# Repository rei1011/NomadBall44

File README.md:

# NomadBall44

## ライセンス

本リポジトリのオリジナル部分は **GNU General Public License v3**（[LICENSE](LICENSE)）です。

## 第三者ソフトウェア・素材

キーボード設計にあたり、以下のオープンソース／クリエイティブ・コモンズの成果物を利用しています。帰属表示、MIT 全文、GPLv3 との関係、CC BY-SA の条項へのリンクは **[NOTICES](NOTICES)** にまとめています。上流ライセンスのコピーは **[third_party/](third_party/)** にも置いています。

| 名称 | 参照 |
|------|------|
| Salicylic-acid3 / KiCAD_FootPrint（MIT） | https://github.com/Salicylic-acid3/KiCAD_FootPrint |
| koktoh / BrownSugar_KBD_KiCad_Library（MIT） | https://github.com/koktoh/BrownSugar_KBD_KiCad_Library |
| kumamuk-git / roBa（GPL-3.0） | https://github.com/kumamuk-git/roBa |
| Seeed Studio / OPL_Kicad_Library（CC BY-SA 4.0） | https://github.com/Seeed-Studio/OPL_Kicad_Library |

Seeed OPL 由来の KiCad シンボル・フットプリントのファイル一覧、改変内容の説明、および派生ファイルを単体で再配布する際の表示の目安は、**[NOTICES](NOTICES)** のセクション 4 に記載しています。

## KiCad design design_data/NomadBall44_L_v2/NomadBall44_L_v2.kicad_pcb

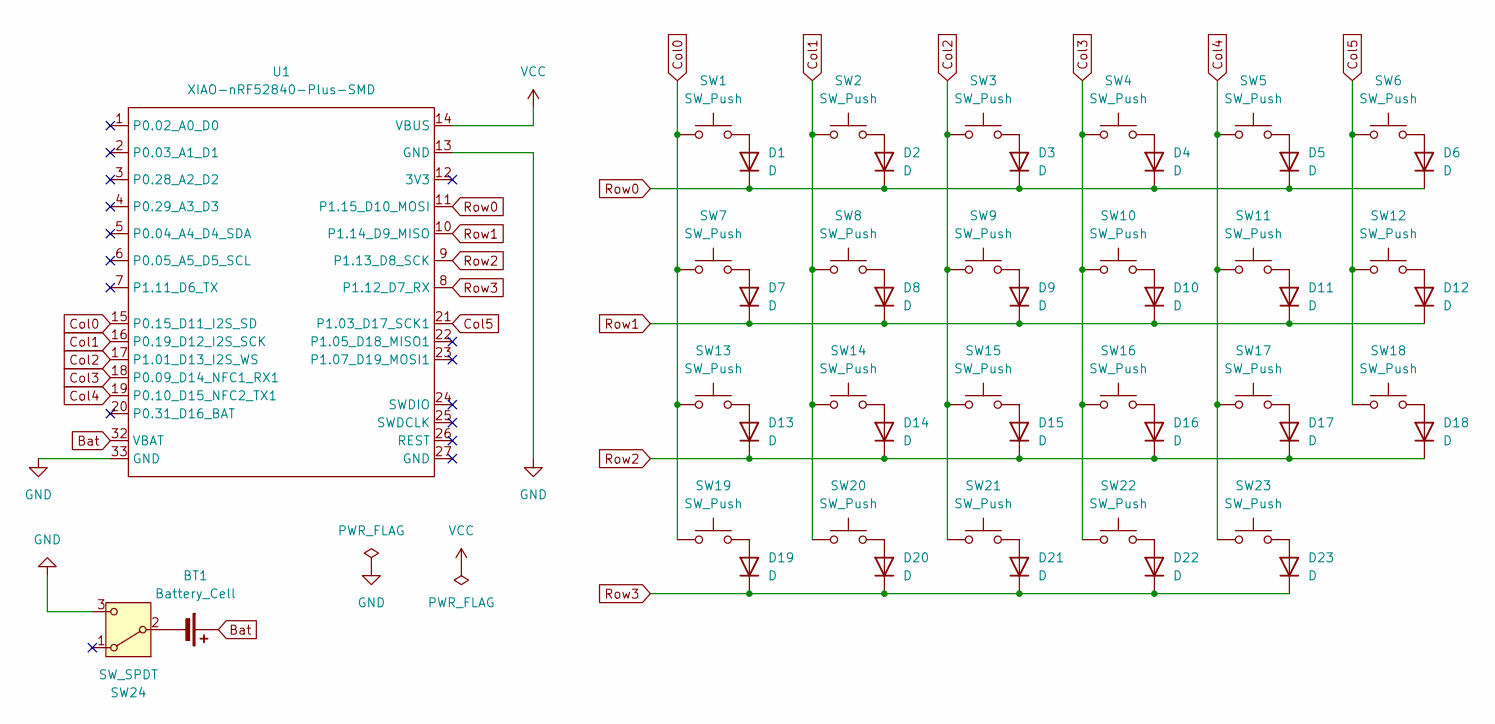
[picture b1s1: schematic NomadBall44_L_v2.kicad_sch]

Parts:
BT1: Battery_Cell; JST_S2B-PH-SM4-TB
D1, D2, D3, D4, D5, D6, D7, D8, D9, D10, D11, D12, D13, D14, D15, D16, D17, D18, D19, D20, D21, D22, D23: D; Diode_SMD
SW1, SW2, SW3, SW4, SW5, SW6, SW7, SW8, SW9, SW10, SW11, SW12, SW13, SW14, SW15, SW16, SW17, SW18, SW19, SW20, SW21, SW22, SW23: SW_Push; Choc_v2_Hotswap_1u
SW24: SW_SPDT; TGSW_MSK-12D19
U1: XIAO-nRF52840-Plus-SMD; XIAO-nRF52840-Plus-ver3

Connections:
Bat: BT1.1 (+), U1.32 (VBAT)
Col0: SW1.1, SW7.1, SW13.1, SW19.1, U1.15 (P0.15_D11_I2S_SD)
Col1: SW2.1, SW8.1, SW14.1, SW20.1, U1.16 (P0.19_D12_I2S_SCK)
Col2: SW3.1, SW9.1, SW15.1, SW21.1, U1.17 (P1.01_D13_I2S_WS)
Col3: SW4.1, SW10.1, SW16.1, SW22.1, U1.18 (P0.09_D14_NFC1_RX1)
Col4: SW5.1, SW11.1, SW17.1, SW23.1, U1.19 (P0.10_D15_NFC2_TX1)
Col5: SW6.1, SW12.1, SW18.1, U1.21 (P1.03_D17_SCK1)
GND: SW24.3 (C), U1.13 (GND), U1.33 (GND)
unnamed: BT1.2 (-), SW24.2 (B)
unnamed: D1.2 (A), SW1.2
unnamed: D2.2 (A), SW2.2
unnamed: D3.2 (A), SW3.2
unnamed: D4.2 (A), SW4.2
unnamed: D5.2 (A), SW5.2
unnamed: D6.2 (A), SW6.2
unnamed: D7.2 (A), SW7.2
unnamed: D8.2 (A), SW8.2
unnamed: D9.2 (A), SW9.2
unnamed: D10.2 (A), SW10.2
unnamed: D11.2 (A), SW11.2
unnamed: D12.2 (A), SW12.2
unnamed: D13.2 (A), SW13.2
unnamed: D14.2 (A), SW14.2
unnamed: D15.2 (A), SW15.2
unnamed: D16.2 (A), SW16.2
unnamed: D17.2 (A), SW17.2
unnamed: D18.2 (A), SW18.2
unnamed: D19.2 (A), SW19.2
unnamed: D20.2 (A), SW20.2
unnamed: D21.2 (A), SW21.2
unnamed: D22.2 (A), SW22.2
unnamed: D23.2 (A), SW23.2
Row0: D1.1 (K), D2.1 (K), D3.1 (K), D4.1 (K), D5.1 (K), D6.1 (K), U1.11 (P1.15_D10_MOSI)
Row1: D7.1 (K), D8.1 (K), D9.1 (K), D10.1 (K), D11.1 (K), D12.1 (K), U1.10 (P1.14_D9_MISO)
Row2: D13.1 (K), D14.1 (K), D15.1 (K), D16.1 (K), D17.1 (K), D18.1 (K), U1.9 (P1.13_D8_SCK)
Row3: D19.1 (K), D20.1 (K), D21.1 (K), D22.1 (K), D23.1 (K), U1.8 (P1.12_D7_RX)
VCC: U1.14 (VBUS)

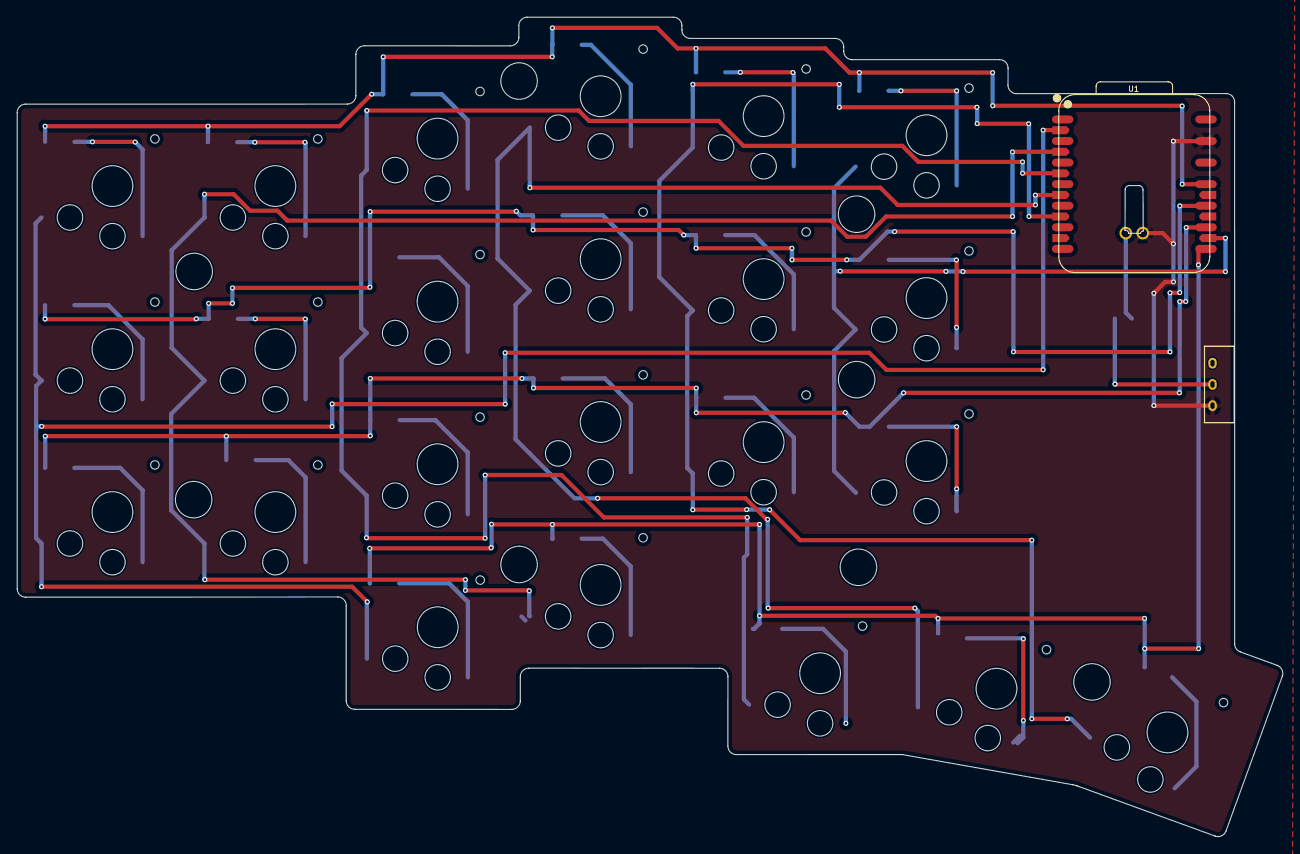
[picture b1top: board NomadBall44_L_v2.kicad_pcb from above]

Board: 2 copper layers, 149.0 x 96.5 mm, 49 parts (1 on the bottom side), 36 nets.

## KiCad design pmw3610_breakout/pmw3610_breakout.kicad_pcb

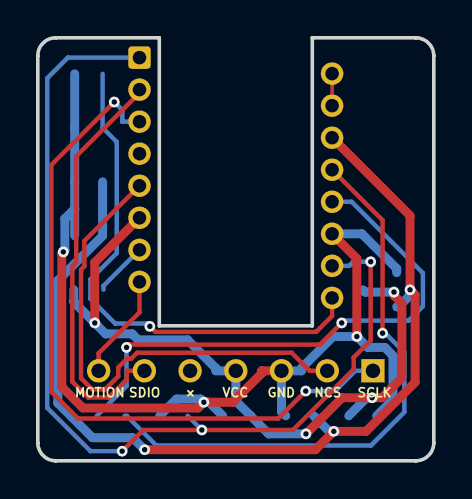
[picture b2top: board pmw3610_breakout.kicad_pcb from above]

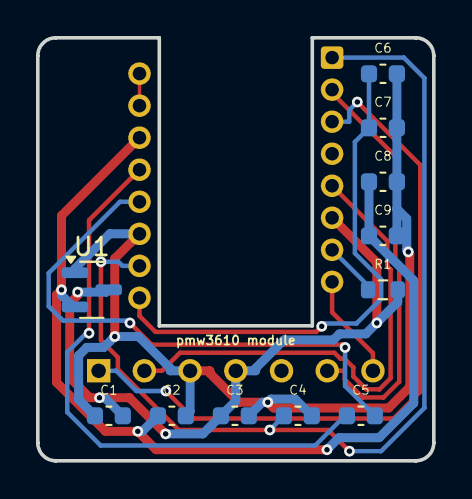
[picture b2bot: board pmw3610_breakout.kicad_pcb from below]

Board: 2 copper layers, 22.0 x 23.5 mm, 13 parts (11 on the bottom side), 13 nets.

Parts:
C1, C2: 1u; C_0603_1608Metric
C3, C5, C8: 100n; C_0603_1608Metric
C4, C7: 10n; C_0603_1608Metric
C6: 10u (X7R); C_0603_1608Metric
C9: 3.3u/25V; C_0603_1608Metric
J1: Conn_01x08; pmw3610_connector_b
R1: 10k; R_0603_1608Metric
U1: MCP1700T-1802E/TT; SOT-23
U2: PMW3610; PMW3610DM-SUDU 16Pin

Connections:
+1V9: C2.1, C8.1, C9.1, U1.2 (VO), U2.14 (VDD)
GND: C1.1, C2.2, C3.2, C4.2, C6.2, C7.2, C8.2, C9.2, J1.3, U1.1 (GND), U2.11 (GND)
MOTION: J1.7 (Pin_6), U2.8 (MOTION)
NCS: J1.2, U2.5 (NCS)
unnamed: C4.1, U2.1 (+VCSEL), U2.10 (PASS_T)
unnamed: U2.15 (XYLASER), U2.16 (-VCSEL)
unnamed: C5.1, U2.13 (CN)
unnamed: C5.2, U2.12 (CP)
unnamed: R1.1, U2.7 (NRESET)
unnamed: C6.1, C7.1, U2.9 (VCP)
SCLK: J1.1, U2.3 (SCLK)
SDIO: J1.6, U2.2 (SDIO)
VCC: C1.2, C3.1, J1.4, R1.2, U1.3 (VI), U2.6 (VDDIO)

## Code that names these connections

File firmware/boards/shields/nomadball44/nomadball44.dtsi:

/*
 * NomadBall44 - Common definitions for left and right halves
 * 4x6 matrix, col2row, same pin assignment for both halves
 */

#include <dt-bindings/zmk/matrix_transform.h>

/* xiao_ble default peripheral conflicts - disable to free pins */
&uart0 { status = "disabled"; };
&i2c1  { status = "disabled"; };
&spi2  { status = "disabled"; };

/ {
	kscan: kscan {
		compatible = "zmk,kscan-gpio-matrix";
		wakeup-source;
		diode-direction = "col2row";

		row-gpios
			= <&gpio1 15 (GPIO_ACTIVE_HIGH | GPIO_PULL_DOWN)>  /* Row0: D10 P1.15 */
			, <&gpio1 14 (GPIO_ACTIVE_HIGH | GPIO_PULL_DOWN)>  /* Row1: D9  P1.14 */
			, <&gpio1 13 (GPIO_ACTIVE_HIGH | GPIO_PULL_DOWN)>  /* Row2: D8  P1.13 */
			, <&gpio1 12 (GPIO_ACTIVE_HIGH | GPIO_PULL_DOWN)>  /* Row3: D7  P1.12 */
			;

		col-gpios
			= <&gpio0 15 GPIO_ACTIVE_LOW>   /* Col0: D11 P0.15 */
			, <&gpio0 19 GPIO_ACTIVE_LOW>   /* Col1: D12 P0.19 */
			, <&gpio1 1  GPIO_ACTIVE_LOW>   /* Col2: D13 P1.01 */
			, <&gpio0 9  GPIO_ACTIVE_LOW>   /* Col3: D14 P0.09 */
			, <&gpio0 10 GPIO_ACTIVE_LOW>   /* Col4: D15 P0.10 */
			, <&gpio1 3  GPIO_ACTIVE_LOW>   /* Col5: D17 P1.03 */
			;

		debounce-press-ms = <5>;
		debounce-release-ms = <5>;
	};
};

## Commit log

2026-03-03 右側の電子回路図を作成
2026-03-05 nRF52840 Plus用のフットプリントを作成
2026-03-06 トラックボール基板発注ようにIC部品を割り当て
2026-03-06 jlcpcbdディレクトリをignore
2026-03-06 kicadプロジェクトで管理不要なファイルをgitignoreへ追加
2026-03-06 ビルドガイドのアウトラインを作成
2026-03-06 prlファイルはgitで管理不要なのでgitignoreに指定した
2026-03-06 抵抗が大きすぎたので修正
2026-03-06 ロータリエンコーダーのフットプリントを割り当て
2026-03-06 必要な部品を書き出し
2026-03-06 ライセンスを追加
2026-03-07 NomadBall44用のシンボルライブラリを作成
2026-03-07 pmw3610のコネクター用フットプリントを追加
2026-03-07 シンボルとフットプリントのライブラリのパスを修正
2026-03-07 キースイッチのシンボルにフットプリントを割り当て
2026-03-07 水平スライドスイッチのフットプリントを追加
2026-03-07 デバッグするためにリファレンスフィールドを表示するようにした
2026-03-07 キースイッチのフットプリントを配置
2026-03-07 キーソケットの位置を微調整
2026-03-07 pmw3610のコネクタの位置を微調整
2026-03-07 スライドスイッチとロータリーエンコーダーの位置を微修正
2026-03-08 ビルドガイドに基盤作業に関する簡単な手順を追加
2026-03-08 スペーサーを追加
2026-03-08 水平スライドスイッチの位置を修正
2026-03-08 スペーサーの位置を修正
2026-03-08 電源用の配線定義を追加
2026-03-08 スペーサー用のホール位置を修正
2026-03-08 スペーサー用のフットプリントを追加
2026-03-09 ボトムプレート用のkicadファイルを作成
2026-03-09 外形線にノイズが入っていたので除去
2026-03-09 外形線を微修正
2026-03-10 ボトムプレートの作成
2026-03-10 トッププレートのネジ穴とスイッチ穴を設定
2026-03-10 トッププレート用のkicad projectを作成
2026-03-10 ロータリーエンコーダーの位置を微修正
2026-03-10 トッププレートからダイオードのフットプリントを削除
2026-03-10 PCB基盤の外形線を修正
2026-03-10 トラックボール用の配線を追加 & 端面スルーホール向けに導体から基板端のクリアランスを0に設定
2026-03-10 トラックボールとバッテリー周りを配線
2026-03-10 マイコンまわりの配線が完了 & ラベルの間違えを修正
2026-03-10 キースイッチまわりの配線完了
2026-03-11 不要なファイルを削除
2026-03-11 トッププレート用のkicadプロジェクトを作成
2026-03-11 スイッチホールとネジ用ホールを設定
2026-03-11 ダイオードを削除
2026-03-11 配線を削除
2026-03-11 トッププレートに不要なエリアを削除
2026-03-11 親指用トッププレート用のプロジェクトを作成
2026-03-11 ダイオードの削除 & キーホールとネジ用ホールを設定
2026-03-11 親指用の外形線を作成
2026-03-11 ボトムプレート用の外形線を削除
2026-03-11 ダイオードとキースイッチのフットプリントを削除
2026-03-11 ネジ用ホールを設定
2026-03-11 不要な配線を削除
2026-03-11 PHコネクタとバッテリー用のエリアを作成
2026-03-11 ネジ穴を一つ追加
2026-03-11 keyballのボトムケースデータを読み込み
2026-03-11 m1.9用のネジ穴を追加 & PHコネクタ用のエリアを修正
2026-03-11 端面スルーホール用のnrf52840のフットプリントを追加
2026-03-11 左手PCB基板用のプロジェクトを作成
2026-03-11 左手用の回路図を作成
2026-03-11 フットプリントの割り当てを更新
2026-03-11 PCB基盤のガーバファイルを生成
2026-03-11 ボトムプレートのガーバファイルを生成
2026-03-11 トッププレートのガーバファイルを生成
2026-03-11 トッププレート（親指）のガーバファイルを生成
2026-03-11 左手キーボードのフットプリントをインポート
2026-03-11 右側PCBのレイアウトを反転さ左側PCBに配置
2026-03-11 キースイッチを一部配置
2026-03-11 外形線とスペーサーの位置を修正
2026-03-11 PHコネクタを反転
2026-03-12 ダイオードを配置
2026-03-12 マイコン周りのフットプリントを配置
2026-03-12 バッテリー周りの配線を修正
2026-03-12 マイコン周りの配線を実施
2026-03-12 キースイッチの配線が完了
2026-03-12 PCB基板発注用のファイルを生成
2026-03-12 トッププレート用のプロジェクトを作成
2026-03-12 トッププレート完成
2026-03-12 トッププレート（親指）の作成
2026-03-12 ボトムプレートのプロジェクトを作成
2026-03-12 ボトムプレートを作成
2026-03-12 トッププレートのガーバファイルとドリルファイルを生成
2026-03-12 トッププレート（親指）のガーバファイルとドリルファイルを生成
2026-03-12 PCB基盤のガーバファイルとドリルファイルを生成
2026-03-12 ボトムプレートのガーバファイルとドリルファイルを生成
2026-03-12 ボトムプレートの位置を修正
2026-03-12 ボトムプレートのガーバファイルとドリルファイルを修正
2026-03-12 pwr flagを追加
2026-03-12 抵抗値を微修正
2026-03-13 注文用のデータを生成
2026-03-13 発注用のデータを格納するディレクトリ名を変更
2026-03-13 発注用のデータをgit管理から除外 & ディレクトリ名を修正
2026-03-14 シンボルライブラリのパスを変更
2026-03-14 refactor: KiCad関連ディレクトリを design_data/ へ移行
    - lib, NomadBall44_L, NomadBall44_L_Bottom, NomadBall44_L_Top
    - NomadBall44_L_Top_Thumb, NomadBall44_R, NomadBall44_R_Bottom
    - NomadBall44_R_Top, NomadBall44_R_Top_Thumb, pmw3610_breakout
    を design_data/ 配下に移動
    Made-with: Cursor
2026-03-14 ファームウェア用のディレクトリを作成
2026-03-15 Nomadball44のfirmwareを作成
2026-03-15 ビルドエラーを修正
2026-03-15 github actions上での警告を修正
2026-03-16 firmwareを作成
2026-03-26 マイコンに関する改変を明記
2026-04-01 nrf52840 plus用の新しいfootprintを作成
2026-04-01 新しい左手基板のkicadプロジェクトを作成
2026-04-01 新しい右手基板のkicadプロジェクトを作成
2026-04-01 右手基板のスライドスイッチのGNDパットの位置を変更
2026-04-01 nrf52840 plusのfootprintを改良
2026-04-01 nrf52840 plusのfootprintを変更し配線を修正
2026-04-01 右手基板のシンボルとフットプリントの紐付けを修正
2026-04-01 左手基板のマイコンfootprintを変更し配線を修正
2026-04-01 DRCで発生したエラーを修正
2026-04-01 chocv1をchocv2に変更
2026-04-01 キースイッチの配置を修正
2026-04-01 ダイオードの配置を修正
2026-04-01 キースイッチをchocv1からchocv2へ変更
2026-04-01 シンボルとフットプリントの紐付けを修正
2026-04-02 左手基板のキー位置を修正
2026-04-02 BAT用の配線を微修正
2026-04-02 導体から基盤端のクリアランスをデフォルト値に戻した
2026-04-02 スペーサーの位置を微修正
2026-04-02 DRCのエラーを修正
2026-04-02 スイッチ番号の表記位置を修正
2026-04-02 右手のボトムプレートプロジェクト作成
2026-04-02 キースイッチとダイオードを削除
2026-04-02 ネジ穴を追加
2026-04-02 トラックボールケース用のネジ穴を設定
2026-04-02 ボトムプレートに不要なfootprintやedge cutsを削除
2026-04-02 右手基板のボトムプレート用freecadファイルを作成
2026-04-03 不要なレイヤーを削除
2026-04-03 バッテリーとPHコネクタ用のポケットを作成
2026-04-03 ネジ穴のポケットを作成
2026-04-03 薄い箇所が0.8mm（jlpcbの制限値）以下になっていたので修正
2026-04-03 左手基板のボトムプレート用プロジェクトを作成
2026-04-03 配線を削除しネジ穴を設定
2026-04-03 不要なフットプリントを削除
2026-04-03 dxfファイルを出力
2026-04-03 左手ボトムプレート用のfreecadプロジェクトを作成
2026-04-03 左手ボトムプレート用の3Dモデルを作成
2026-04-03 左手トッププレート用のkiccadプロジェクト作成
2026-04-04 不要なフットプリントと配線を削除
2026-04-04 左手トッププレート完成
2026-04-04 左手トップープレート（親指）完成
2026-04-04 ノイズ対策でGNDで塗りつぶし
2026-04-04 右手PCB基板のgerberファイルを生成
2026-04-04 gndの塗りつぶしを実行
2026-04-04 gerberファイルの吐き出し
2026-04-04 ポケットを微修正
2026-04-04 トッププレートのネジ穴フットプリントを変更
2026-04-04 トッププレートの外形線を微修正
